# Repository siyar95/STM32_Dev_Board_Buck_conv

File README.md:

# STM32 Dev Board – Project 2

This project is a custom **development board** designed around the **STM32F405RGT** microcontroller.  
It includes the essential peripherals for firmware development and prototyping:

## 🔧 Features

- **STM32F405RGT** ARM Cortex-M3 microcontroller
- **USB (Device/Power)**
- **UART** interface for serial communication
- **SWD (Single Wire Debug)** header for programming and debugging
- **I2C** interface for peripheral communication
- **Buck converter** for stable and effecient 3.3V power supply

## 🧱 PCB Stackup

This project uses a 4-layer PCB design:

1. **Top Layer (Layer 1)** – Signal  
2. **Inner Layer 1 (Layer 2)** – Ground (GND)  
3. **Inner Layer 2 (Layer 3)** – 3.3V Power Plane  
4. **Bottom Layer (Layer 4)** – Signal

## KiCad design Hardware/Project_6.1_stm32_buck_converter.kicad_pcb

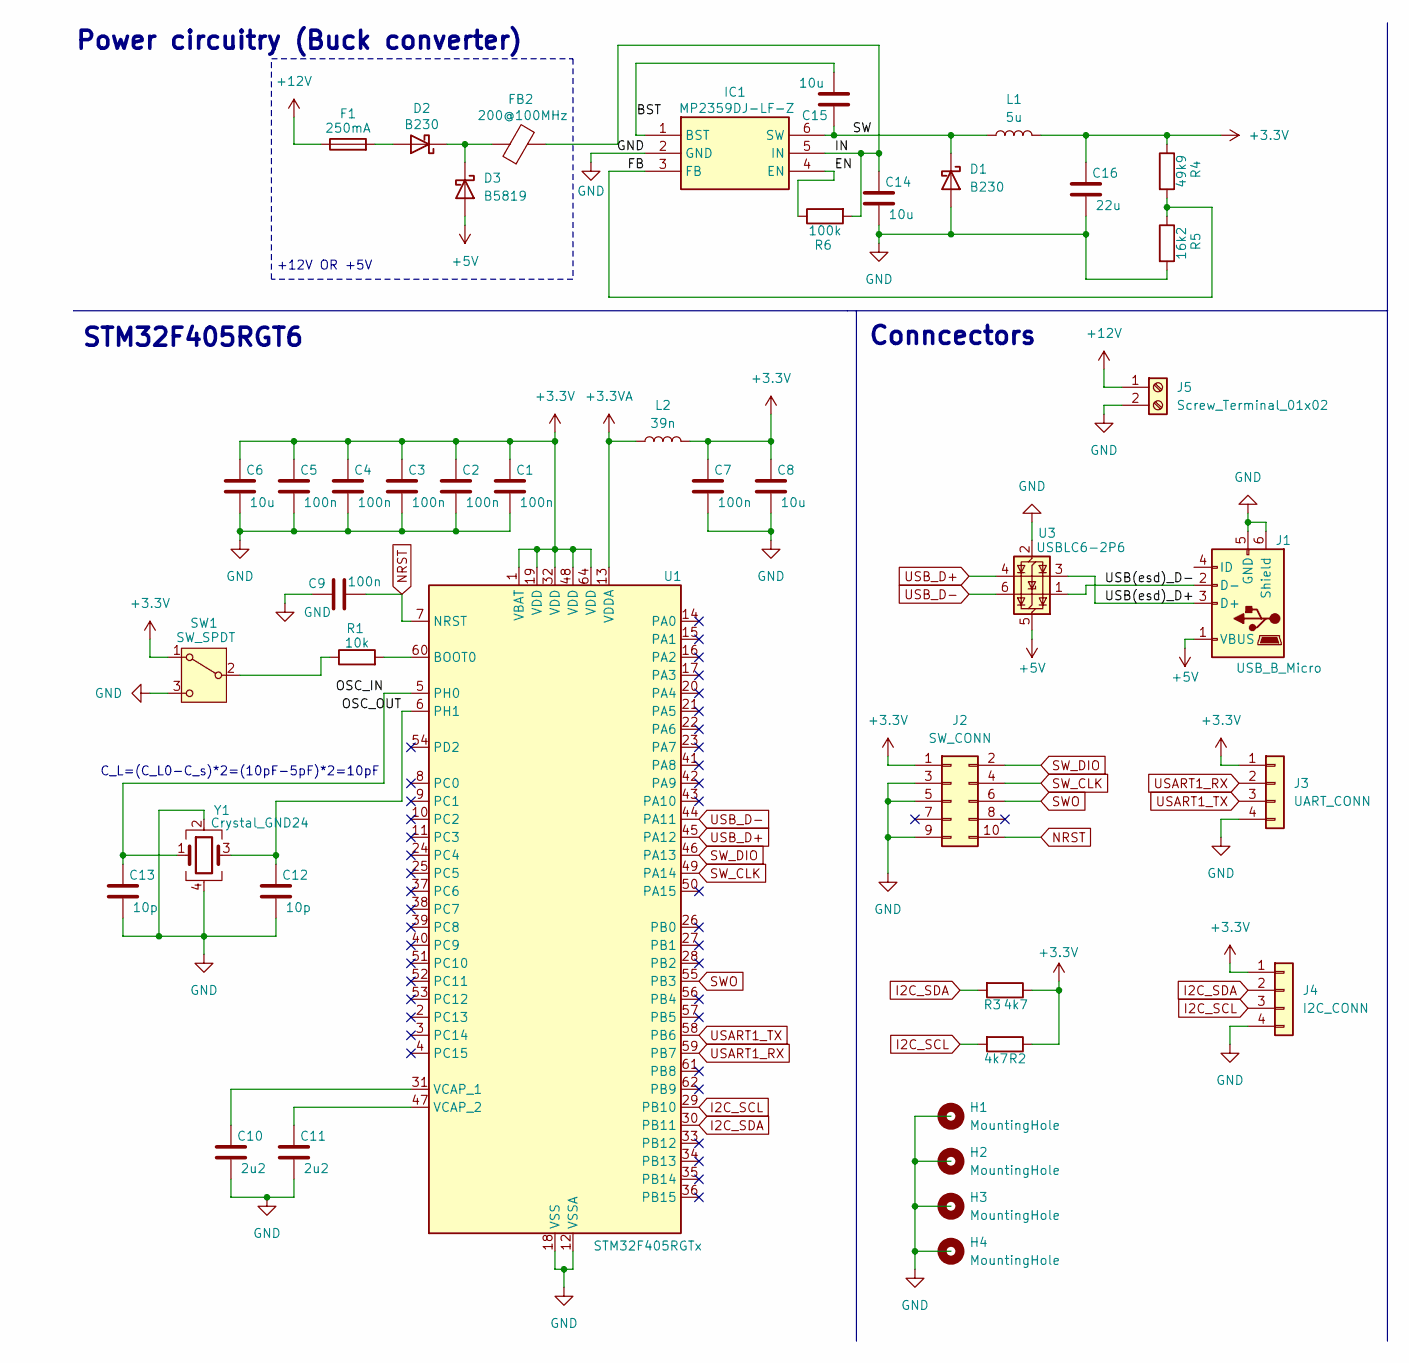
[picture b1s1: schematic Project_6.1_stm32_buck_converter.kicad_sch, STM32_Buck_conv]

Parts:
C1, C2, C3, C4, C5, C7, C9: 100n; C_0402_1005Metric
C6, C8, C14, C15: 10u; C_0603_1608Metric
C10, C11: 2u2; C_0603_1608Metric
C12, C13: 10p; C_0402_1005Metric
C16: 22u; C_0805_2012Metric
D1, D2: B230; D_SMB
D3: B5819; b5819
F1: 250mA; Fuse_0603_1608Metric
FB2: 200@100MHz; L_0603_1608Metric
H1, H2, H3, H4: MountingHole; MountingHole_2.2mm_M2
IC1: MP2359DJ-LF-Z; SOT95P280X100-6N; Mouser Part Number 946-MP2359DJLFZ
J1: USB_B_Micro; USB_Micro-B_Amphenol_10118193-0001LF_Horizontal
J2: SW_CONN; PinHeader_2x05_P2.54mm_Vertical
J3: UART_CONN; PinHeader_1x04_P2.54mm_Vertical
J4: I2C_CONN; PinHeader_1x04_P2.54mm_Vertical
J5: Screw_Terminal_01x02; TerminalBlock_Phoenix_MPT-0,5-2-2.54_1x02_P2.54mm_Horizontal
L1: 5u; L_0603_1608Metric
L2: 39n; L_0402_1005Metric
R1: 10k; R_0603_1608Metric
R2, R3: 4k7; R_0603_1608Metric
R4: 49k9; R_0603_1608Metric
R5: 16k2; R_0603_1608Metric
R6: 100k; R_0603_1608Metric
SW1: SW_SPDT; SW_SPDT_PCM12
U1: STM32F405RGTx; LQFP-64_10x10mm_P0.5mm
U3: USBLC6-2P6; SOT-666
Y1: Crystal_GND24; Crystal_SMD_Abracon_ABM3C-4Pin_5.0x3.2mm

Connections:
+3.3V: C1.1, C2.1, C3.1, C4.1, C5.1, C6.1, C7.1, C8.1, C16.1, J2.1, J3.1, J4.1, L1.2, L2.2, R2.1, R3.1, R4.1, SW1.1 (A), U1.1 (VBAT), U1.19 (VDD), U1.32 (VDD), U1.48 (VDD), U1.64 (VDD)
+3.3VA: L2.1, U1.13 (VDDA)
+5V: D3.2 (A), J1.1 (VBUS), U3.5 (VBUS)
+12V: F1.1, J5.1
/BST: C15.2, IC1.1 (BST)
/EN: IC1.4 (EN), R6.1
/FB: IC1.3 (FB), R4.2, R5.1
/IN: C14.1, FB2.2, IC1.5 (IN), R6.2
/OSC_IN: C13.1, U1.5 (PH0), Y1.1
/OSC_OUT: C12.1, U1.6 (PH1), Y1.3
/SW: C15.1, D1.1 (K), IC1.6 (SW), L1.1
/USB(esd)_D+: J1.3 (D+), U3.3 (I/O2)
/USB(esd)_D-: J1.2 (D-), U3.1 (I/O1)
GND: C1.2, C2.2, C3.2, C4.2, C5.2, C6.2, C7.2, C8.2, C9.1, C10.2, C11.2, C12.2, C13.2, C14.2, C16.2, D1.2 (A), IC1.2 (GND), J1.5 (GND), J1.6 (Shield), J2.3, J2.5, J2.9, J3.4, J4.4, J5.2, R5.2, SW1.3 (C), U1.12 (VSSA), U1.18 (VSS), U1.63 (VSS), U3.2 (GND), Y1.2, Y1.4
I2C_SCL: J4.3, R2.2, U1.29 (PB10)
I2C_SDA: J4.2, R3.2, U1.30 (PB11)
NRST: C9.2, J2.10, U1.7 (NRST)
unnamed: D2.2 (A), F1.2
unnamed: D2.1 (K), D3.1 (K), FB2.1
unnamed: R1.1, SW1.2 (B)
unnamed: R1.2, U1.60 (BOOT0)
unnamed: C10.1, U1.31 (VCAP_1)
unnamed: C11.1, U1.47 (VCAP_2)
SWO: J2.6, U1.55 (PB3)
SW_CLK: J2.4, U1.49 (PA14)
SW_DIO: J2.2, U1.46 (PA13)
USART1_RX: J3.2, U1.59 (PB7)
USART1_TX: J3.3, U1.58 (PB6)
USB_D+: U1.45 (PA12), U3.4 (I/O2)
USB_D-: U1.44 (PA11), U3.6 (I/O1)

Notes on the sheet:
+12V OR +5V
STM32F405RGT6
Power circuitry (Buck converter)
Conncectors
C_L=(C_L0-C_s)*2=(10pF-5pF)*2=10pF

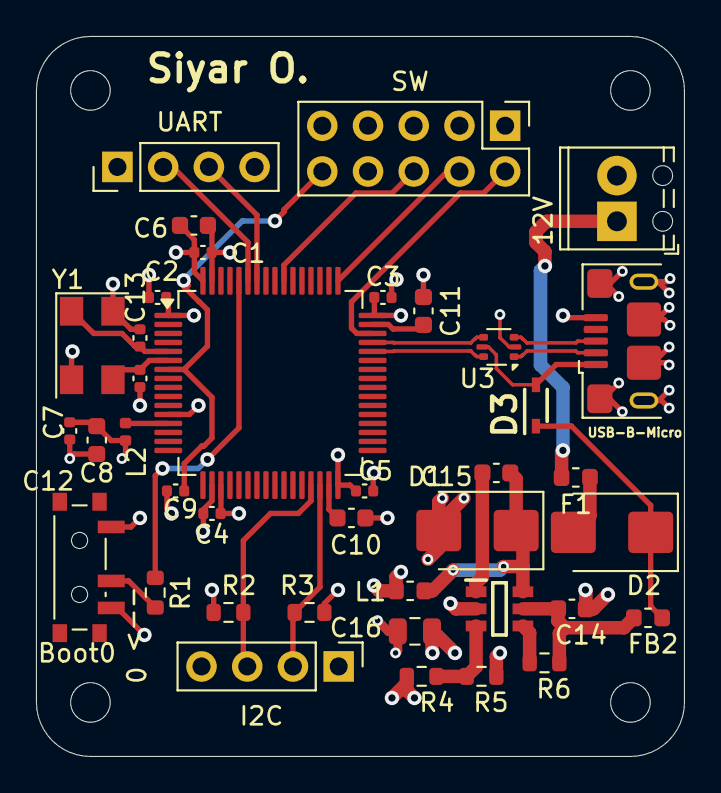
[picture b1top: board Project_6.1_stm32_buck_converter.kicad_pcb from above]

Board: 4 copper layers, 36.0 x 40.0 mm, 43 parts (0 on the bottom side), 30 nets.

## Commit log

2025-05-06 Rename Project_6.1_stm32_buck_converter.kicad_pro to Hardware/Project_6.1_stm32_buck_converter.kicad_pro
